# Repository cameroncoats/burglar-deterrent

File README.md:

#Eversafe
Engineering Product Design for Uni

Design for a 'smart timer'; plug-through switch intended to turn lamps on & off etc to create the appearance of an occupied house and deter burglary.

Got an alright mark for this so it would appear we did something right

**Group Project - other members are not named here for their own privacy**

## Structure
* web - web app & server side code
* embedded - embedded code and associated files
* hardware - for enclosure, pcb etc design files
* artwork - for branding, logos etc

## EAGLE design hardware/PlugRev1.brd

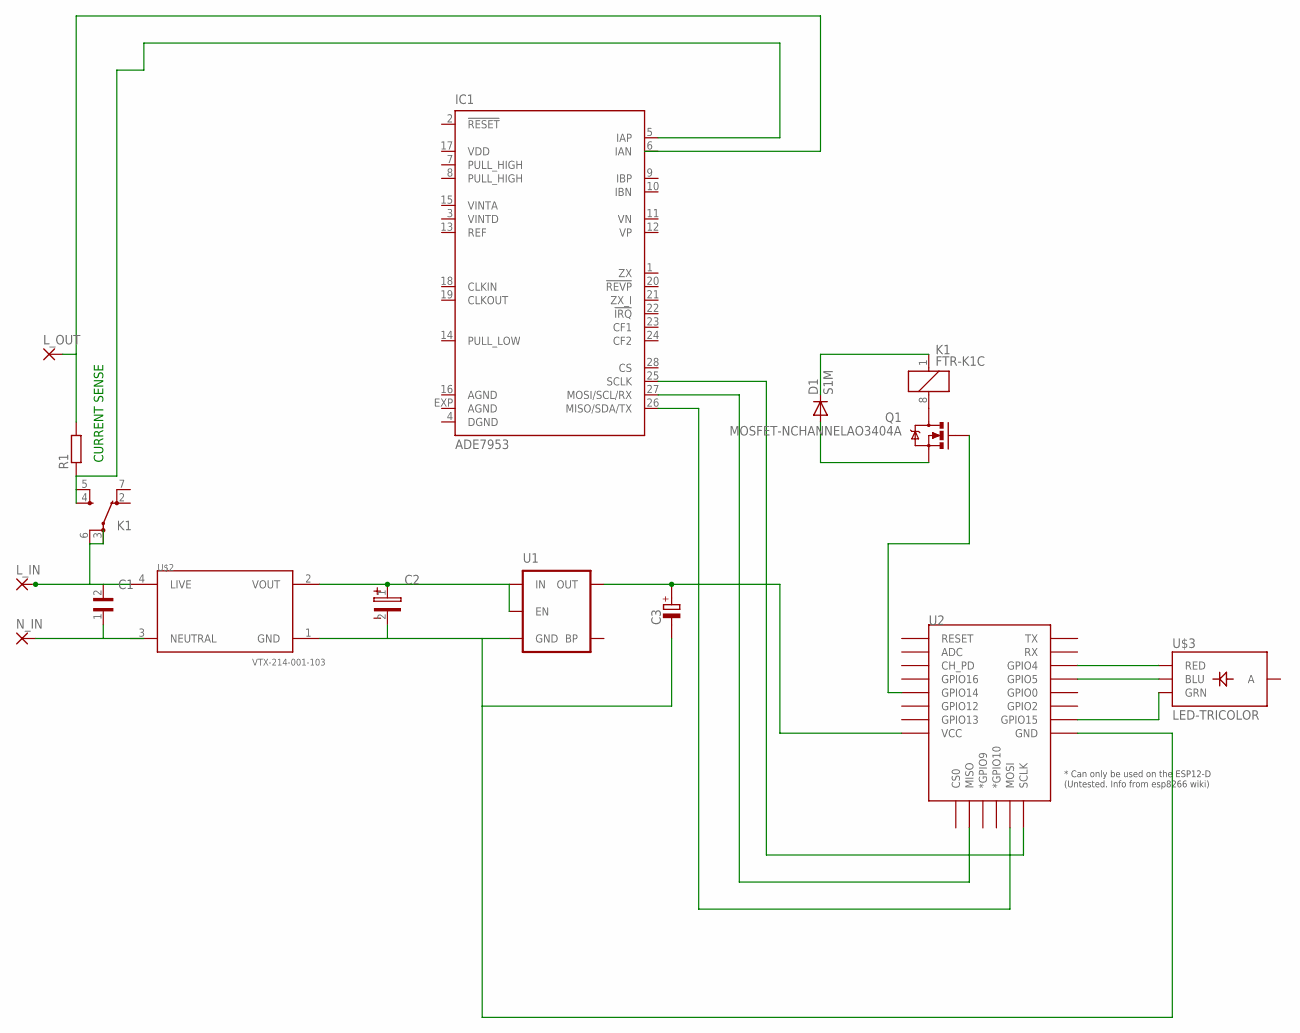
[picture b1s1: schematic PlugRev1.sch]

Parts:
C1: WCAP-FTX2_890324023024CS; WCAP-FTX2_10X13X13X7
C2: WCAP-ASLI_6.3X5.5(DXL); 3.5X1.6X2.1(BXCXA)
C3: POLARISED_CASE_A; CAPAE330X540N
D1: S1M; SMA
IC1: ADE7953; QFN28-ML
K1: FTR-K1C
L_IN: 3,81/1,4
L_OUT: 3,81/1,4
N_IN: 3,81/1,4
Q1: MOSFET-NCHANNELAO3404A; SOT23-3
R1: R-EU_R3216; R3216
U1: MIC52053.3V; SOT23-5
U2: ESP12ESMD; ESP12E-SMD
U$2: VTX-214-001-103; VTX214001103
U$3: LED-TRICOLOR; LED-TRICOLOR-SMD

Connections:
AGND: IC1.16 (AGND), IC1.EXP (AGND)
DGND: IC1.4 (DGND)
GND: C2.2, C3.-, U1.2 (GND), U2.GND, U$2.1 (GND)
unnamed: C3.+, U1.5 (OUT), U2.VCC
unnamed: IC1.5 (IAP), K1.4 (SA), K1.5 (SB), R1.1
unnamed: C1.1, N_IN.1
unnamed: C1.2, K1.6 (PB), L_IN.1, U$2.4 (LIVE)
unnamed: K1.8 (2), Q1.3 (D)
unnamed: D1.C, K1.1
unnamed: D1.A, Q1.2 (S)
unnamed: L_OUT.1, R1.2
unnamed: IC1.26 (MISO/SDA/TX), U2.MOSI
unnamed: IC1.27 (MOSI/SCL/RX), U2.MISO
unnamed: IC1.25 (SCLK), U2.SCLK
unnamed: Q1.1 (G), U2.GPIO14
unnamed: U2.GPIO4, U$3.R (RED)
unnamed: U2.GPIO5, U$3.B (BLU)
unnamed: U2.GPIO15, U$3.G (GRN)
VDD: IC1.17 (VDD)
VOUT: C2.1, U1.1 (IN), U1.3 (EN), U$2.2 (VOUT)

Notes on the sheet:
CURRENT SENSE

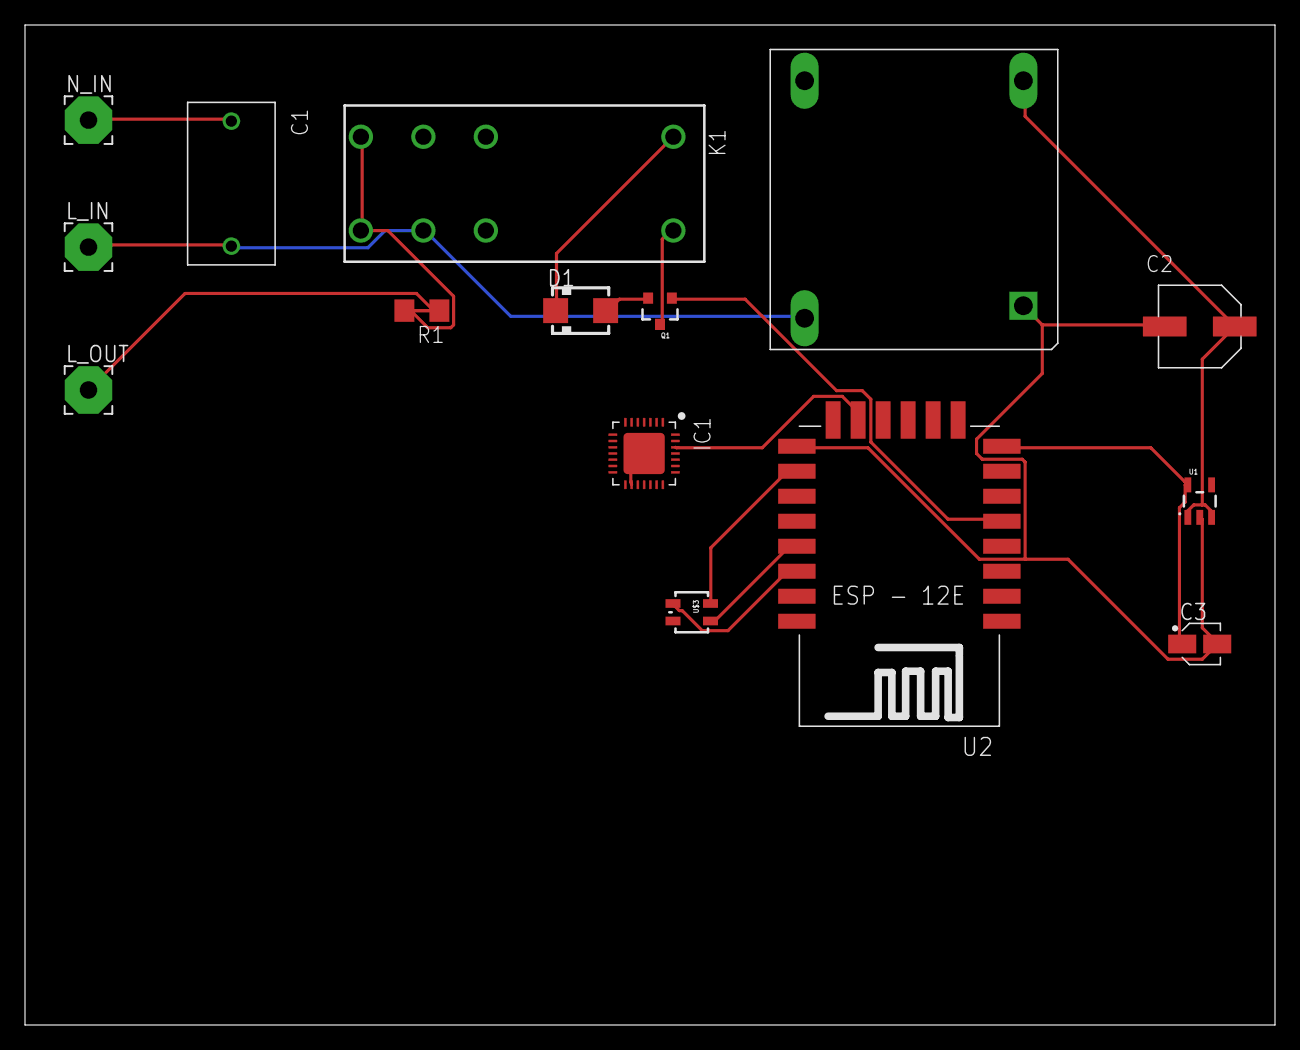
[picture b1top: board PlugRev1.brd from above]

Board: 2 copper layers, 100.0 x 80.0 mm, 15 parts (0 on the bottom side), 18 nets.

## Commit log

2015-09-29 add description to read
2015-09-29 missed closing i tag
2015-09-29 button styling
2015-09-29 button logic
2015-09-29 toast on state change
2015-09-29 fixes
2015-09-29 missing ;
2015-09-29 extra {
2015-09-29 call functions on click
2015-09-29 responsiveness
2015-09-29 remove container
2015-09-29 inject toasty
2015-09-29 adjust desktop width
2015-09-29 viewport!
2015-09-29 show alert for longer
2015-09-29 limit to one toast
2015-09-29 initial commit of API
2015-09-29 some API fixes
2015-09-29 rename model
2015-09-29 update to get functionality
2015-09-29 fix get action
2015-09-29 provide context on buttons & disable when selected
2015-09-29 context fix
2015-09-29 check for button position in functions
2015-09-29 variable name fix
2015-09-29 change operator
2015-09-29 update database on click
2015-09-29 load status from api
2015-09-29 button not buttons
2015-09-29 remove profanity
2015-09-29 branding & fa-fw
2015-09-29 nav fix
2015-09-29 limit toastyness
2016-01-31 branding & beautify
2016-01-31 readme & organisation
2016-01-31 keep empty dirs in repo
2016-02-01 added placeholder icon
2016-02-01 update readme
    Test asana integration
    https://app.asana.com/0/85721228882879/85721228882880
2016-02-01 initial commit of embedded LUA
2016-02-02 add energy metering view & remove app branding
    https://app.asana.com/0/85721230119972/85721228882886
2016-02-02 add energy link to navbar
    https://app.asana.com/0/85721230119972/85721228882886
2016-02-02 add graphing
    https://app.asana.com/0/85721230119972/85721228882886
2016-02-02 add chart.js
2016-02-02 add energy metering
2016-02-02 encode data
2016-02-02 don't encode data & remove semicolon
2016-02-02 add watt suffix
2016-02-02 read only
2016-02-02 series labels
2016-02-02 fix suffix
2016-02-02 responsive layout
2016-02-02 didn't fit on screen, refactor
2016-02-02 sort out div tags
2016-02-02 use mysql
2016-02-02 fix navbar srefs
2016-02-02 remove <?php tag added in error
2016-02-02 add database auth
2016-02-02 add settings view
2016-02-02 add to settings view
2016-02-02 missing close div
2016-02-02 add input group to show pound sign
2016-02-02 define models & start on variable rate logic
2016-02-02 normalise model keys
2016-02-02 implement dynamic fieldsets
2016-02-02 remove static definition
2016-02-02 strings in quotes
2016-02-02 repeat for add to fieldset
2016-02-02 define empty array for variable rate billing
2016-02-02 change ng if to ng show
2016-02-02 hardcode variables for debugging
2016-02-02 hardcode more
2016-02-02 inline form for variable rate
2016-02-02 two lines
2016-02-02 add a well for readability
2016-02-02 remove extra label tag
2016-02-02 add ever safe section & remove subheadings
2016-02-02 close i tags
2016-02-03 add logout button & improve settings page formatting
2016-02-03 implement auth0
    https://app.asana.com/0/85721228882879/85721228882882
2016-02-03 remove CDN dependencies
    https://app.asana.com/0/85721228882879/85721228882882
2016-02-03 fix parenthesis
2016-02-03 missing close }
2016-02-03 dependencies
2016-02-03 another dependency
2016-02-04 don't require login to access login page
2016-02-04 add nabber controller to handle logouts
2016-02-04 improve login page & navbar
2016-02-04 fix profile & conditional navbar
2016-02-04 fix profile picture & update login status on login/out
2016-02-04 remove }
2016-02-04 remove ;
2016-02-04 apply main controller globally & update login status when logging in
2016-02-04 remove authprovider
2016-02-04 remove navbar controller & use main controller globally
2016-02-04 remove controller per view & set values of isloggedin and profile more sensibly
2016-02-04 fix profile width
2016-02-04 css syntax, beautify, define profile on each controller run
2016-02-04 handle authenticate event
2016-02-04 add authprovider to mainController
2016-02-04 go to home state on login
2016-02-04 update user info on state change
2016-02-04 move updateinfo
2016-02-04 go to login state when user logs out
2016-02-04 do quotes make a difference?
2016-02-04 also move state go
2016-02-04 injecting $state probably helps more than changing to single quotes
2016-02-04 move settings link to dropdown
2016-02-04 add bootstrap switch
2016-02-04 add switches
2016-02-05 start implementing tsdb
2016-02-05 change settings page layout
2016-02-05 correct request formatting
2016-02-05 correct variable rate billing layout
2016-02-05 inject bootstrap switch & icon fixes
2016-02-05 fix parameter types
2016-02-05 add models for switches
2016-02-05 move to angular for ever safe units
2016-02-05 define switch size
2016-02-05 give switches max height
2016-02-05 fix bootstrap switch css
2016-02-05 conditional classes
2016-02-05 colours and labels
2016-02-05 conditional colours
2016-02-05 remove refs
2016-02-06 start implementing TSDB graph
2016-02-06 tsdb controller
2016-02-06 add get plugs method
2016-02-06 correct query
2016-02-06 remove debugging
2016-02-06 get the name as well
2016-02-06 use dynamic data in app
2016-02-06 syntax and loading handler
2016-02-06 switch from bool to string
2016-02-08 start tsdb calculations
2016-02-08 forgot to object
2016-02-08 some debugging
2016-02-08 add getMostRecent
2016-02-08 used wrong field name
2016-02-08 query tweaks
2016-02-08 debugging
2016-02-08 send ADC value in place of power
2016-02-08 Correct query for current power
2016-02-08 undebug
2016-02-09 add get most recent power for user
2016-02-09 Change interval to 60s
2016-02-09 missing semicolon
2016-02-09 load energyNow dynamically
2016-02-09 syntax
2016-02-09 implement getLastDay && fix getLastWeek
2016-02-09 forgot to update function name
2016-02-09 start documenting
2016-02-09 slightly better debugging
2016-02-09 even slightly better debugging
2016-02-09 implement getLastDay in controller & use a less ridiculous way of routing requests
2016-02-09 indents & fix variable
2016-02-09 comments and better debugging
2016-02-09 fix debugging yet again
2016-02-11 corrections & debugging
2016-02-11 add order by statement
2016-02-11 make sure power is 0 if not otherwise defined
2016-02-11 debug start & end time
2016-02-23 hardware initial commit
2016-04-22 first round of changes for demo
2016-04-22 bugfixes
2016-04-22 fix button logic
2016-04-22 more button logic
2016-04-22 use labels instead of <small>
2016-04-22 assign -> compare & resize
2016-04-22 label resizing
2016-04-22 update every 5 seconds
2016-04-22 inject store provider
2016-04-22 remove store as it's not a provider
2016-04-22 run local storage getter in controller
2016-04-22 auth interventions
2016-04-22 syntax again
2016-04-22 try to fix login again
2016-04-22 ensure scope updates
2016-04-22 add backdoor
2016-04-22 more fixes
2016-04-23 implement getSimpleStatus for esp
2016-04-23 complicate simpleStatus
2016-04-23 Alerting logic
2016-04-23 client side alerting
2016-04-23 fix typo
2016-04-23 don't add duplicate alerts
2016-04-23 more accurate power measuring
2016-04-23 fix parameter names
2016-04-23 font size hack
2016-04-23 font size hack pt 2
2016-04-23 remove rotate test
2016-04-23 reduce graph to one series
2016-04-23 fix not recording data when plug off
2017-02-11 Sanitise database credentials
2017-02-11 Add comment

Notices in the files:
parts and their libraries:
Wurth_Elektronik_Passive_Capacitors_rev1: Copyright: Würth Elektronik
SparkFun-DiscreteSemi: Licensing: Creative Commons ShareAlike 4.0 International - https://creativecommons.org/licenses/by-sa/4.0
